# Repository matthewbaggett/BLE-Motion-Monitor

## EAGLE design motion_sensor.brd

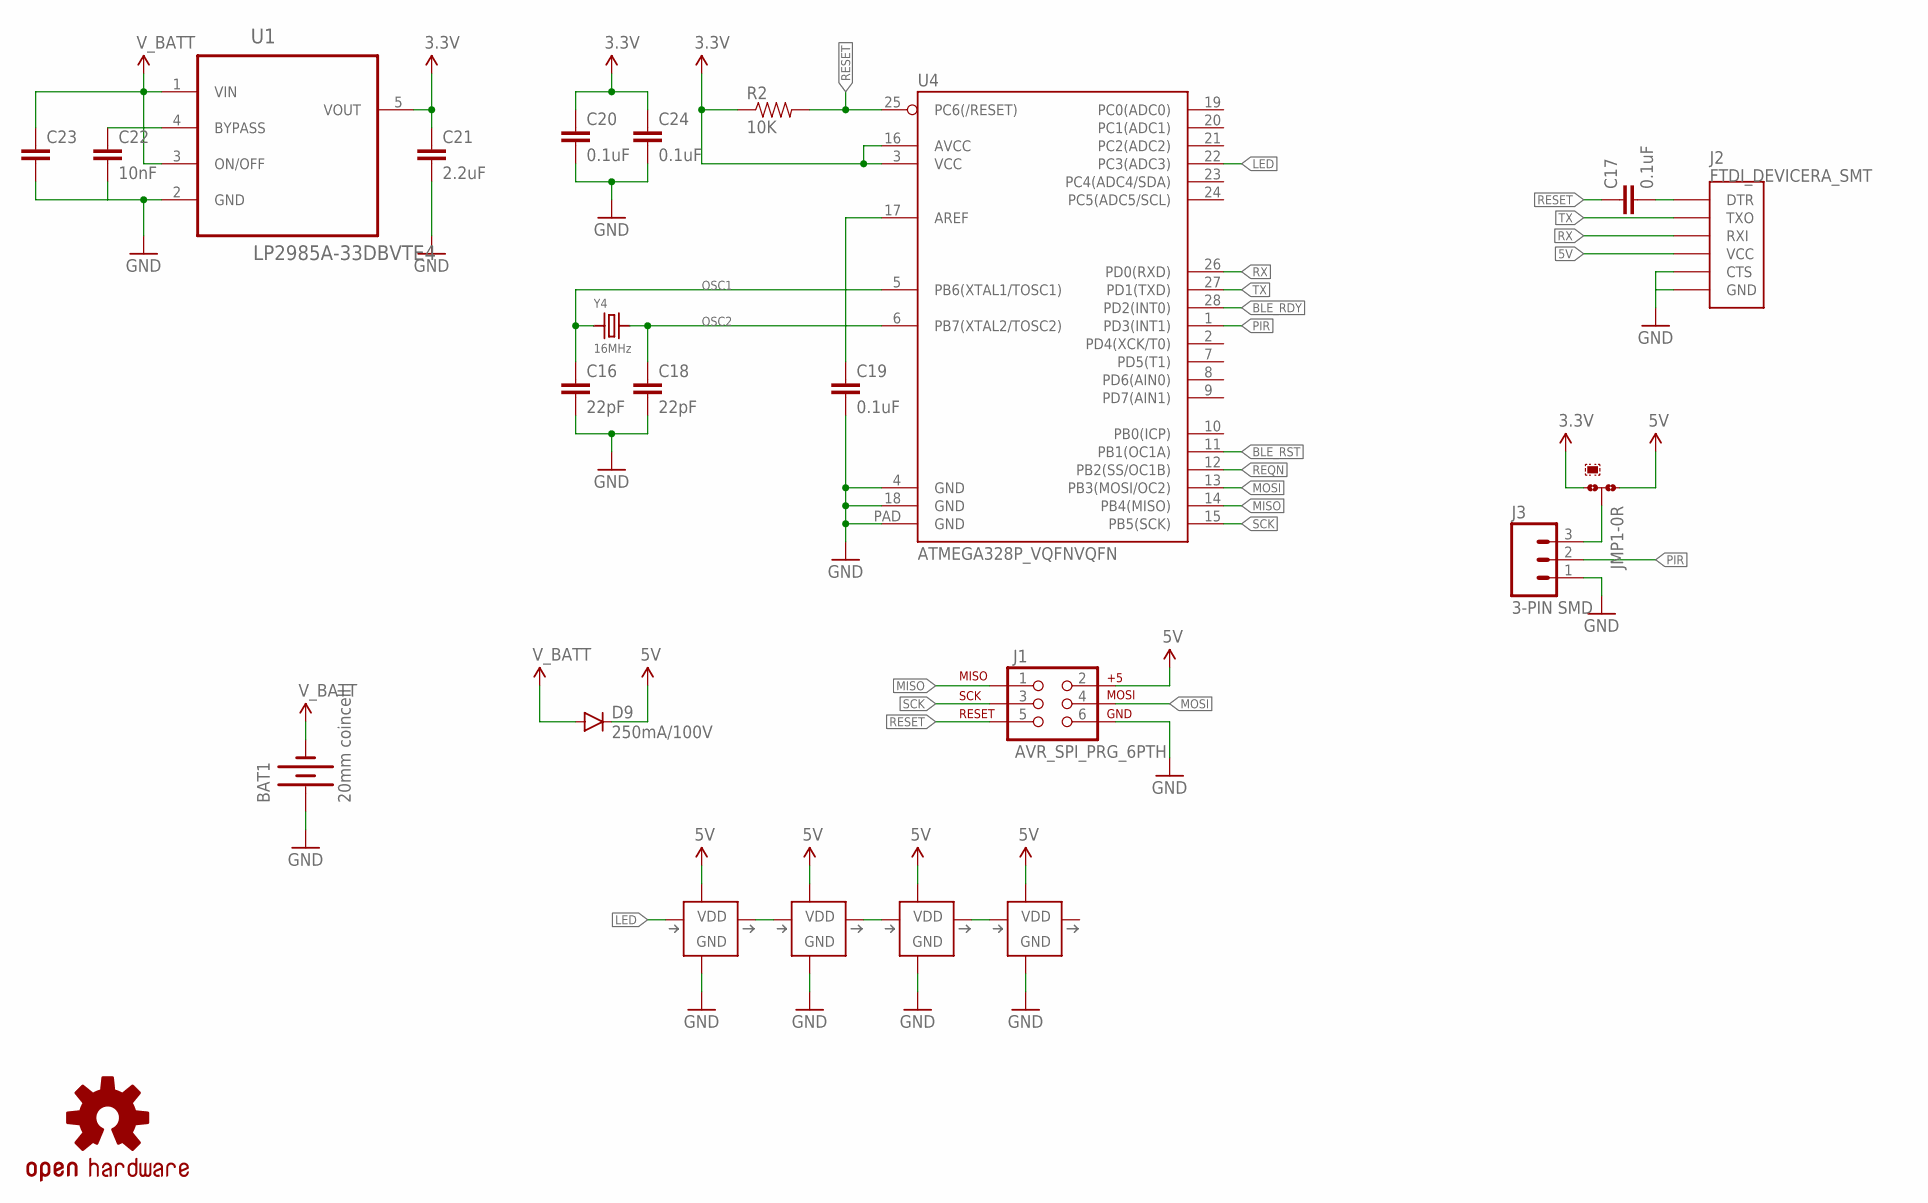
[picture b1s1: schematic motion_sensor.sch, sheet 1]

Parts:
BAT1: 20mm coincell; BATTCON_20MM_4LEGS
C16, C18: 22pF; 0603-CAP
C17, C19, C20, C24: 0.1uF; 0603-CAP
C21: 2.2uF; 0603-CAP
C22: 10nF; 0603-CAP
C23: 1UF-25V-10%(0805)"; 0805-CAP
D9: 250mA/100V; SOD-323
J1: AVR_SPI_PRG_6PTH; 2X3
J2: FTDI_DEVICERA_SMT; FTDI_DEVICE_RA_SMT
J3: 3-PIN SMD; JST-3-SMD
JMP1: 0R-JUMPC; C0R-JMP
LOGO1: OSHW-LOGOS; OSHW-LOGO-S
R2: 10K; 0603-RES
U1: LP2985A-33DBVTE4; SOT95P280X145-5N
U4: ATMEGA328P_VQFNVQFN; VQFN-28
U$1, U$11, U$15, U$17: SK6812MINI; LED-3535
Y4: 16MHz; CRYSTAL_3.2X2.5

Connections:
3.3V: C20.1, C21.1, C24.1, JMP1.3, R2.1, U1.5 (VOUT), U4.3 (VCC), U4.16 (AVCC); also elsewhere on the board
5V: D9.C, J1.2, J2.4 (VCC), JMP1.1, U$1.3 (VDD), U$11.3 (VDD), U$15.3 (VDD), U$17.3 (VDD)
AREF: C19.1, U4.17 (AREF)
BLE_RDY: U4.28 (PD2(INT0)); also elsewhere on the board
BLE_RST: U4.11 (PB1(OC1A)); also elsewhere on the board
BYPASS: C22.1, U1.4 (BYPASS)
DTR: C17.2, J2.1 (DTR)
GND: BAT1.POSITIVE@1 (+), BAT1.POSITIVE@2 (+), BAT1.POSITIVE@3 (+), BAT1.POSITIVE@4 (+), C16.2, C18.2, C19.2, C20.2, C21.2, C22.2, C23.2, C24.2, J1.6, J2.5 (CTS), J2.6 (GND), J3.1, U1.2 (GND), U4.4 (GND), U4.18 (GND), U4.PAD (GND), U$1.1 (GND), U$11.1 (GND), U$15.1 (GND), U$17.1 (GND); also elsewhere on the board
LED: U4.22 (PC3(ADC3)), U$1.2 (DI)
MISO: J1.1, U4.14 (PB4(MISO)); also elsewhere on the board
MOSI: J1.4, U4.13 (PB3(MOSI/OC2)); also elsewhere on the board
unnamed: U$1.4 (DO), U$11.2 (DI)
unnamed: U$11.4 (DO), U$15.2 (DI)
unnamed: U$15.4 (DO), U$17.2 (DI)
OSC1: C16.1, U4.5 (PB6(XTAL1/TOSC1)), Y4.1
OSC2: C18.1, U4.6 (PB7(XTAL2/TOSC2)), Y4.2
PIR: J3.2, U4.1 (PD3(INT1))
PIR_VDD: J3.3, JMP1.2
REQN: U4.12 (PB2(SS/OC1B)); also elsewhere on the board
RESET: C17.1, J1.5, R2.2, U4.25 (PC6(/RESET))
RX: J2.3 (RXI), U4.26 (PD0(RXD))
SCK: J1.3, U4.15 (PB5(SCK)); also elsewhere on the board
TX: J2.2 (TXO), U4.27 (PD1(TXD))
V_BATT: BAT1.NEGATIVE (-), C23.1, D9.A, U1.1 (VIN), U1.3 (ON/OFF)

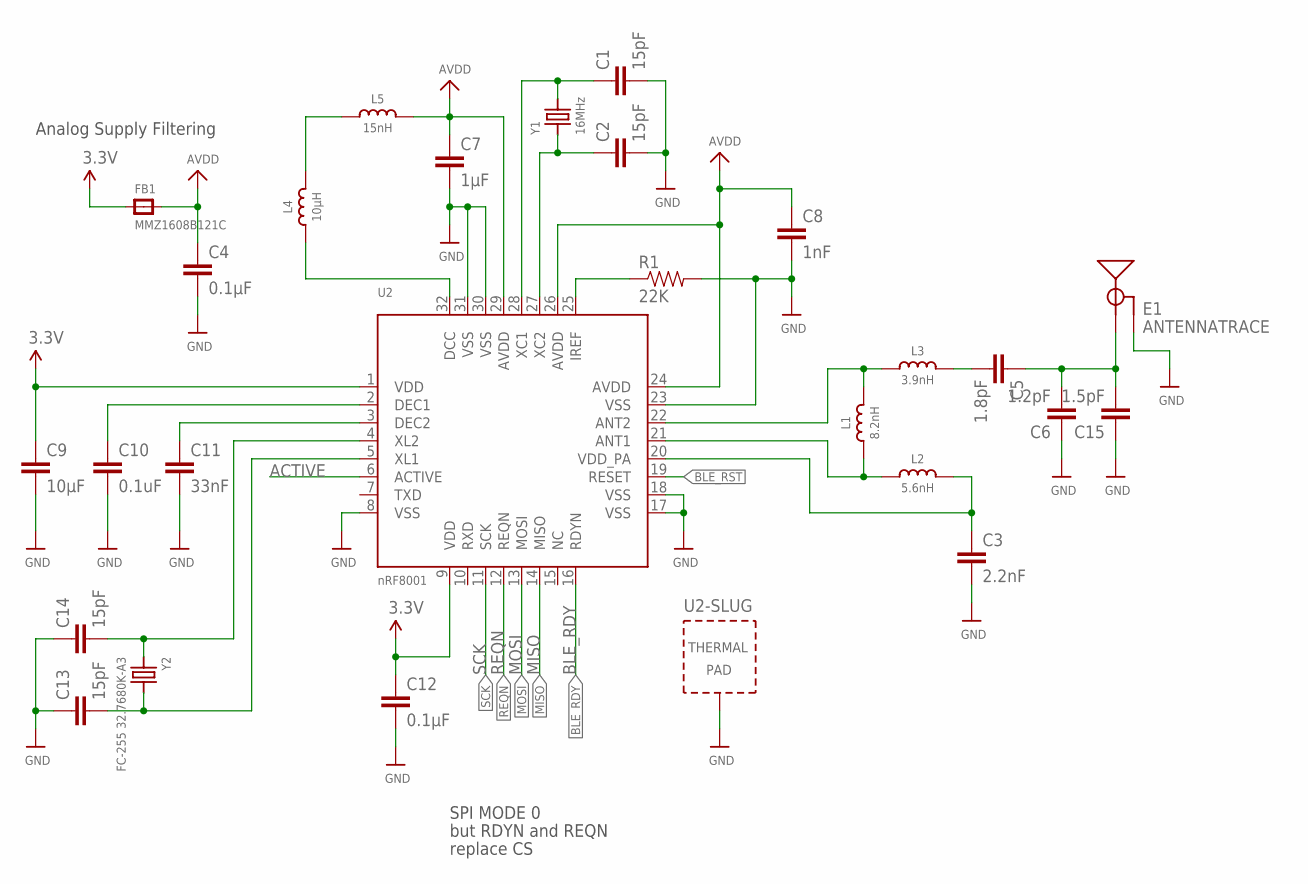
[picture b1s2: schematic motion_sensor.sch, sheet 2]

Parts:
C1, C2, C13, C14: 15pF; 0805
C3: 2.2nF; 0805
C4, C12: 0.1µF; 0805
C5: 1.8pF; 0805
C6: 1.2pF; 0805
C7: 1µF; 0805
C8: 1nF; 0805
C9: 10µF; 0805
C10: 0.1uF; 0805
C11: 33nF; 0805
C15: 1.5pF; 0805
E1: ANTENNATRACE; TRACE_ANTENNA_2.4GHZ_25.7MM
FB1: MMZ1608B121C; 0805
L1: 8.2nH; _0402
L2: 5.6nH; _0402
L3: 3.9nH; _0402
L4: 10µH; _0603
L5: 15nH; _0603
R1: 22K; 0603-RES
U2: nRF8001; QFN32_5MM
Y1: 16MHz; CRYSTAL_3.2X2.5
Y2: FC-255 32.7680K-A3; CRYSTAL_8X3.8

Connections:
3.3V: C9.1, C12.1, FB1.1, U2.1 (VDD), U2.9 (VDD); also elsewhere on the board
???: L4.2, L5.1
ACTIVE: U2.6 (ACTIVE)
AVDD: C4.1, C7.1, C8.1, FB1.2, L5.2, U2.24 (AVDD), U2.26 (AVDD), U2.29 (AVDD)
BLE_RDY: U2.16 (RDYN); also elsewhere on the board
BLE_RST: U2.19 (RESET); also elsewhere on the board
DCC: L4.1, U2.32 (DCC)
DEC1: C10.1, U2.2 (DEC1)
DEC2: C11.1, U2.3 (DEC2)
GND: C1.2, C2.2, C3.2, C4.2, C6.1, C7.2, C8.2, C9.2, C10.2, C11.2, C12.2, C13.1, C14.1, C15.1, E1.GND, E1.GND2 (GND), R1.2, U2.8 (VSS), U2.17 (VSS), U2.18 (VSS), U2.23 (VSS), U2.30 (VSS), U2.31 (VSS), U2.33 (TP); also elsewhere on the board
MISO: U2.14 (MISO); also elsewhere on the board
MOSI: U2.13 (MOSI); also elsewhere on the board
unnamed: R1.1, U2.25 (IREF)
unnamed: C3.1, L2.2, U2.20 (VDD_PA)
unnamed: L1.2, L3.1, U2.22 (ANT2)
unnamed: L1.1, L2.1, U2.21 (ANT1)
unnamed: C5.2, L3.2
unnamed: C5.1, C6.2, C15.2, E1.ANT (SIGNAL)
REQN: U2.12 (REQN); also elsewhere on the board
SCK: U2.11 (SCK); also elsewhere on the board
XC1: C1.1, U2.28 (XC1), Y1.2
XC2: C2.1, U2.27 (XC2), Y1.1
XL1: C13.2, U2.5 (XL1), Y2.P$4 (2)
XL2: C14.2, U2.4 (XL2), Y2.P$1 (1)

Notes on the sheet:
Analog Supply Filtering
SPI MODE 0
but RDYN and REQN
replace CS

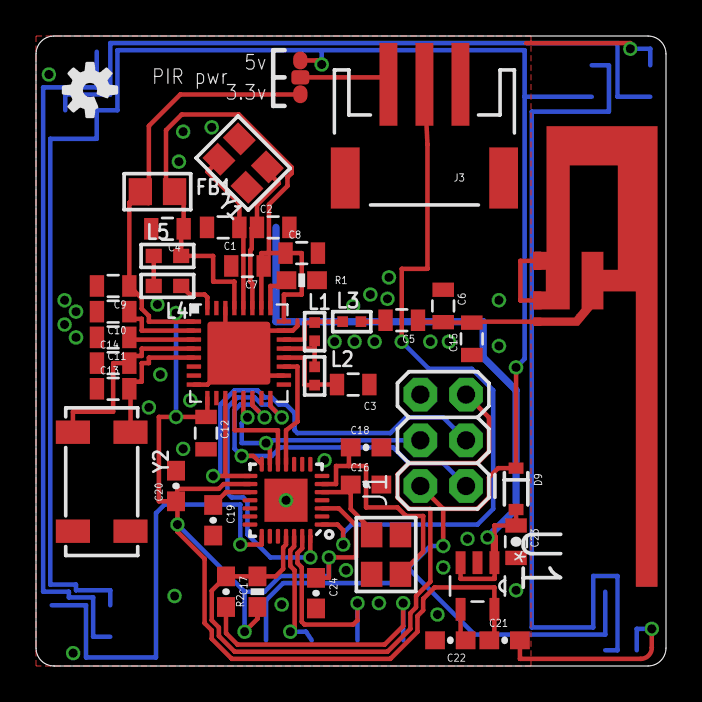
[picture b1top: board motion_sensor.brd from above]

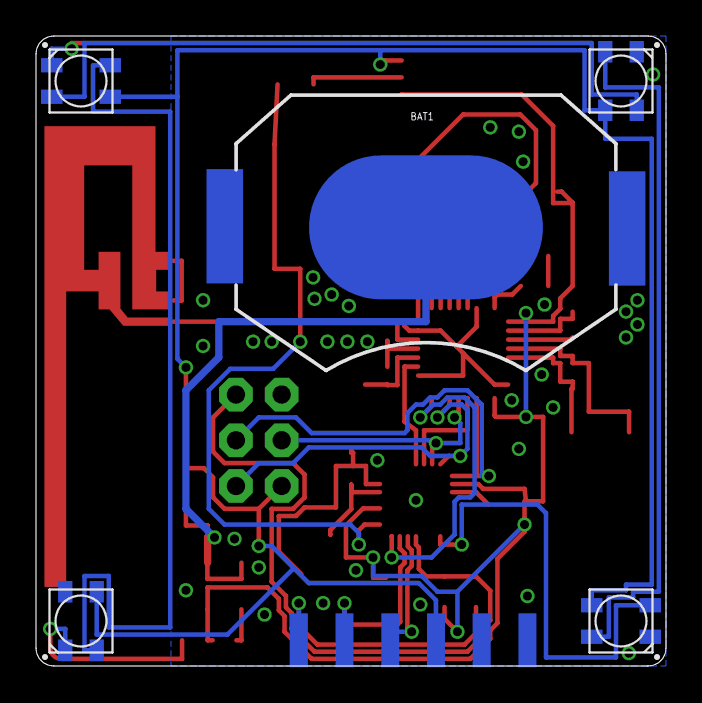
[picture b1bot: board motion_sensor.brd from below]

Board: 2 copper layers, 35.0 x 35.0 mm, 50 parts (6 on the bottom side), 39 nets.

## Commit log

2017-07-12 unfinished schematic
2017-07-12 Move away from esp8266 to ATMEGA328 + nRF8001
2017-07-13 First PCB attempt
2017-07-13 Fixing bug with reset circuit. Add FTDI header.
2017-07-13 Clean up silkscreen
2017-07-13 Respin board to be 35mm square. Better antenna. Less things near the antenna.
2017-07-13 Remove part value labels
2017-07-13 Add OSH logo. Add png versions of schematic and pcb.

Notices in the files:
parts and their libraries:
SparkFun-Electromechanical: Licensing: Creative Commons ShareAlike 4.0 International - https://creativecommons.org/licenses/by-sa/4.0
microbuilder: This work is placed in the public domain, and may be freely used for commercial and non-commercial work with the following conditions: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
